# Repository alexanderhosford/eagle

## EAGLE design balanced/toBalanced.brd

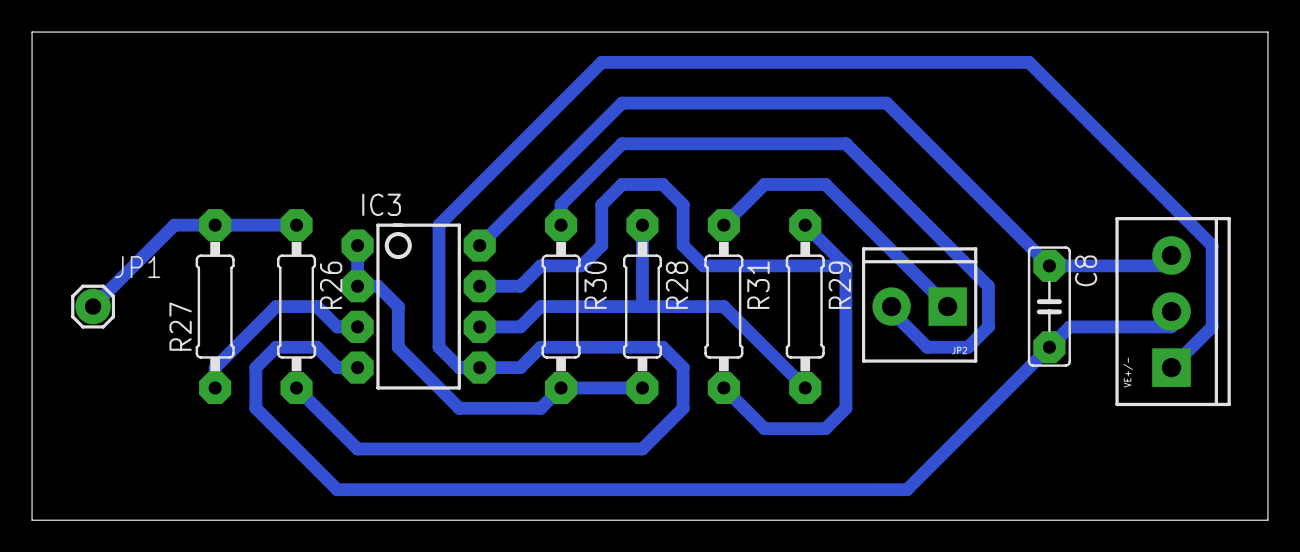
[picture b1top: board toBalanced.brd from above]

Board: 2 copper layers, 77.1 x 30.5 mm, 11 parts (0 on the bottom side), 10 nets.

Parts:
C8: 100nF; C050-025X075
IC3: TL072; DIP08
JP1: INPUT; 1X01
JP2: OUTPUT; SCREWTERMINAL-3.5MM-2
R26, R28, R29: 10k; 0207/10
R27: 2k2; 0207/10
R30, R31: 100r; 0207/10
VE+/-: POWER; SCREWTERMINAL-3.5MM-3

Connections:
15V+: C8.1, IC3.8, VE+/-.3
15V-: C8.2, IC3.4, VE+/-.2
GND: IC3.5, R26.2, VE+/-.1
unnamed: JP1.1, R26.1, R27.2
unnamed: IC3.7, R29.1, R31.2
unnamed: JP2.1, R31.1
unnamed: JP2.2, R30.1
unnamed: IC3.6, R28.1, R29.2
unnamed: IC3.1, IC3.2, R28.2, R30.2
unnamed: IC3.3, R27.1

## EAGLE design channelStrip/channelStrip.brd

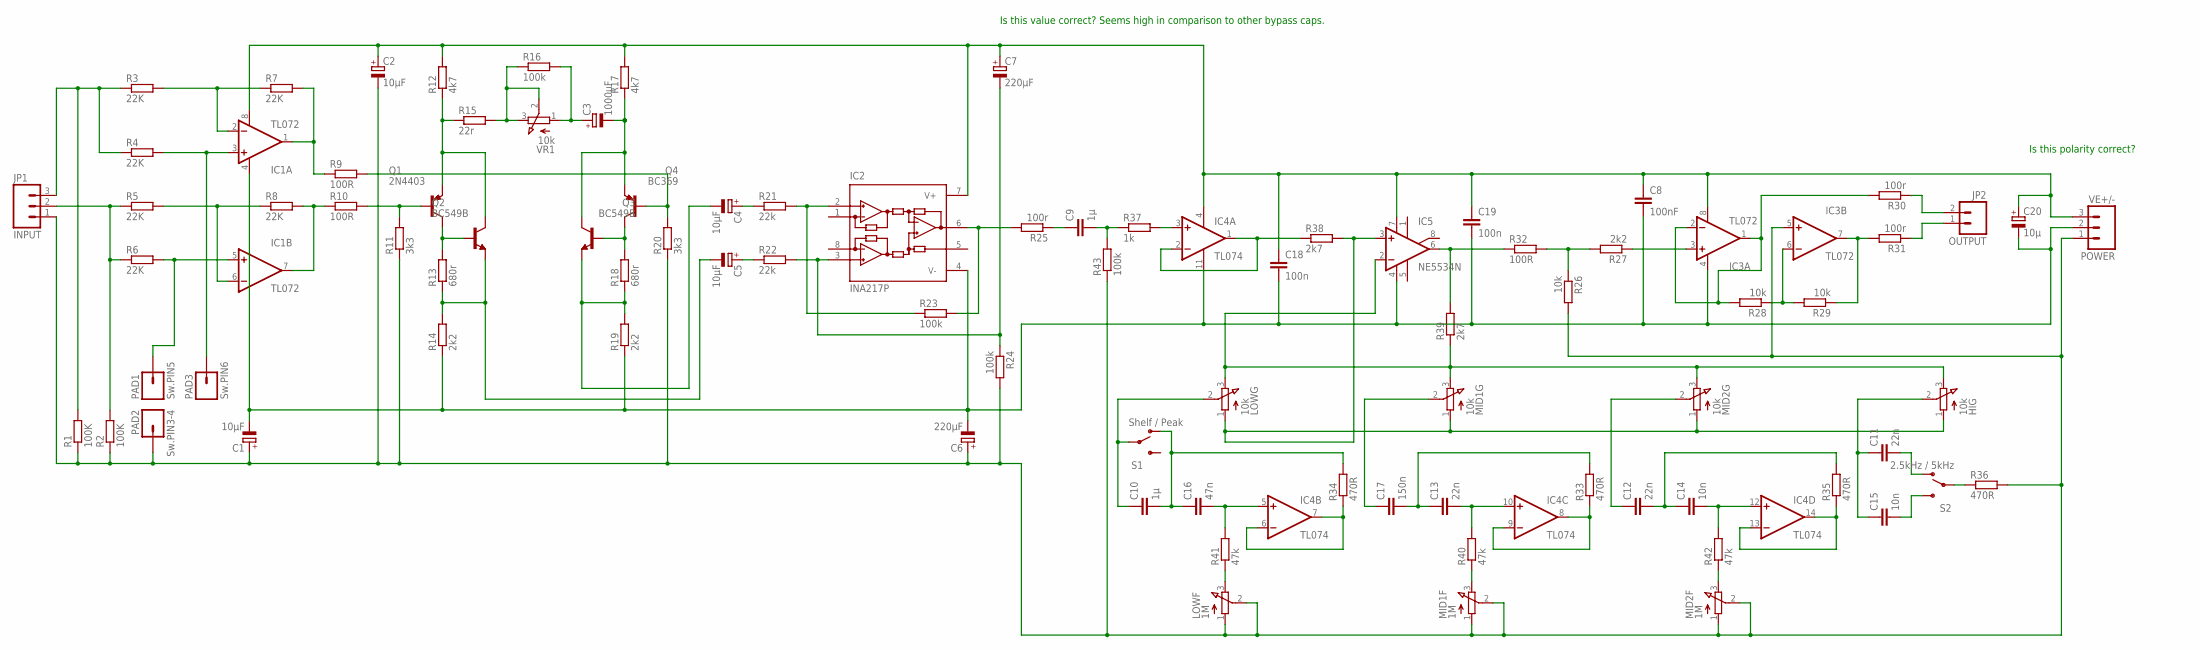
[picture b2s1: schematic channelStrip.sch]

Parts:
C1, C2: 10µF; E2,5-6
C3: 1000µF; E5-10,5
C4, C5: 10µF; E15-5
C6, C7: 220µF; E5-10,5
C8: 100nF; C050-025X075
C9, C10: 1µ; C050-025X075
C11, C12, C13: 22n; C050-025X075
C14, C15: 10n; C050-025X075
C16: 47n; C050-025X075
C17: 150n; C050-025X075
C18, C19: 100n; C050-025X075
C20: 10µ; E2,5-6E
HIG: 10k; 3RP/1610N
IC1, IC3: TL072; DIP08
IC2: INA217P; DIL08
IC4: TL074; DIL14
IC5: NE5534N; DIL08
JP1: INPUT; SCREWTERMINAL-3.5MM-3
JP2: OUTPUT; SCREWTERMINAL-3.5MM-2
LOWF: 1M; 3RP/1610N
LOWG: 10k; 3RP/1610N
MID1F, MID2F: 1M; 3RP/1610N
MID1G, MID2G: 10k; 3RP/1610N
PAD1: Sw.PIN5; 1X01_2MM
PAD2: Sw.PIN3-4; 1X01_2MM
PAD3: Sw.PIN6; 1X01_2MM
Q1: 2N4403; TO92-BCE
Q2, Q3: BC549B; TO92-EBC
Q4: BC369; TO92-BCE
R1, R2: 100K; 0207/10
R3, R4, R5, R6, R7, R8: 22K; 0207/10
R9, R10, R32: 100R; 0207/10
R11, R20: 3k3; 0207/10
R12, R17: 4k7; 0207/10
R13, R18: 680r; 0207/10
R14, R19, R27: 2k2; 0207/10
R15: 22r; 0207/10
R16, R23, R24, R43: 100k; 0207/10
R21, R22: 22k; 0207/10
R25, R30, R31: 100r; 0207/10
R26, R28, R29: 10k; 0207/10
R33, R34, R35, R36: 470R; 0207/10
R37: 1k; 0207/10
R38, R39: 2k7; 0207/10
R40, R41, R42: 47k; 0207/10
S1: Shelf / Peak; SWITCH-SPDT
S2: 2.5kHz / 5kHz; SWITCH-SPDT
VE+/-: POWER; SCREWTERMINAL-3.5MM-3
VR1: 10k; 3RP/1610N

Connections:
15V+: C2.+, C7.+, C8.1, C18.1, C19.1, C20.+, IC1.8 (V+), IC2.7 (V+), IC3.8 (V+), IC4.4 (V+), IC5.7 (V+), R12.2, R17.2, VE+/-.3
15V-: C1.-, C6.-, C8.2, C18.2, C19.2, C20.-, IC1.4 (V-), IC2.4 (V-), IC3.4 (V-), IC4.11 (V-), IC5.4 (V-), R14.1, R19.1, VE+/-.2
GND: C1.+, C2.-, C6.+, IC3.5 (+IN), JP1.1, LOWF.1 (A), LOWF.2 (S), MID1F.1 (A), MID1F.2 (S), MID2F.1 (A), MID2F.2 (S), PAD2.1, R1.1, R2.1, R11.1, R20.1, R24.2, R26.2, R36.2, R43.1, VE+/-.1
unnamed: C12.1, MID2G.2 (S)
unnamed: IC3.7 (OUT), R29.1, R31.2
unnamed: C10.2, C16.1, R34.2, S1.1 (O)
unnamed: C13.1, C17.2, R33.2
unnamed: C12.2, C14.1, R35.2
unnamed: C15.2, S2.3 (S)
unnamed: C11.2, S2.1 (O)
unnamed: R36.1, S2.2
unnamed: IC4.13 (-IN), IC4.14 (OUT), R35.1
unnamed: C14.2, IC4.12 (+IN), R42.2
unnamed: MID2F.3 (E), R42.1
unnamed: C9.1, R25.1
unnamed: C9.2, R37.1, R43.2
unnamed: IC4.3 (+IN), R37.2
unnamed: IC4.1 (OUT), IC4.2 (-IN), R38.1
unnamed: HIG.1 (A), IC5.3 (+IN), LOWG.1 (A), MID1G.1 (A), MID2G.1 (A), R38.2
unnamed: IC5.6 (OUT), R32.1, R39.2
unnamed: R26.1, R27.2, R32.2
unnamed: IC4.6 (-IN), IC4.7 (OUT), R34.1
unnamed: C16.2, IC4.5 (+IN), R41.2
unnamed: LOWF.3 (E), R41.1
unnamed: C10.1, LOWG.2 (S), S1.2
unnamed: IC4.8 (OUT), IC4.9 (-IN), R33.1
unnamed: C13.2, IC4.10 (+IN), R40.2
unnamed: MID1F.3 (E), R40.1
unnamed: HIG.3 (E), IC5.2 (-IN), LOWG.3 (E), MID1G.3 (E), MID2G.3 (E), R39.1
unnamed: C11.1, C15.1, HIG.2 (S)
unnamed: JP2.1, R31.1
unnamed: JP2.2, R30.1
unnamed: C7.-, IC2.3 (+IN), R22.2, R24.1
unnamed: IC3.6 (-IN), R28.1, R29.2
unnamed: IC3.1 (OUT), IC3.2 (-IN), R28.2, R30.2
unnamed: IC3.3 (+IN), R27.1
unnamed: C4.+, R21.1
unnamed: IC2.6 (OUT), R23.2, R25.2
unnamed: IC2.2 (-IN), R21.2, R23.1
unnamed: C5.+, R22.1
unnamed: R15.2, R16.1, VR1.2 (S), VR1.3 (E)
unnamed: C3.+, R16.2, VR1.1 (A)
unnamed: C3.-, Q3.C, Q4.E, R17.1
unnamed: Q1.E, Q2.C, R12.1, R15.1
unnamed: Q3.B, Q4.C, R18.2
unnamed: IC1.1 (OUT), R7.2, R9.1
unnamed: Q1.C, Q2.B, R13.2
unnamed: C5.-, Q2.E, R13.1, R14.2
unnamed: IC1.7 (OUT), R8.2, R10.1
unnamed: C4.-, Q3.E, R18.1, R19.2
unnamed: Q4.B, R9.2, R20.2
unnamed: Q1.B, R10.2, R11.2
unnamed: IC1.6 (-IN), R5.2, R8.1
unnamed: IC1.2 (-IN), R3.2, R7.1
unnamed: IC1.5 (+IN), PAD1.1, R6.2
unnamed: IC1.3 (+IN), PAD3.1, R4.2
unnamed: JP1.3, R1.2, R3.1, R4.1
unnamed: JP1.2, R2.2, R5.1, R6.1
VIA1: C17.1, MID1G.2 (S)

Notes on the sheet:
Is this polarity correct?
Is this value correct? Seems high in comparison to other bypass caps.

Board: 2 copper layers, 88 parts (0 on the bottom side), 59 nets, no tracks yet.

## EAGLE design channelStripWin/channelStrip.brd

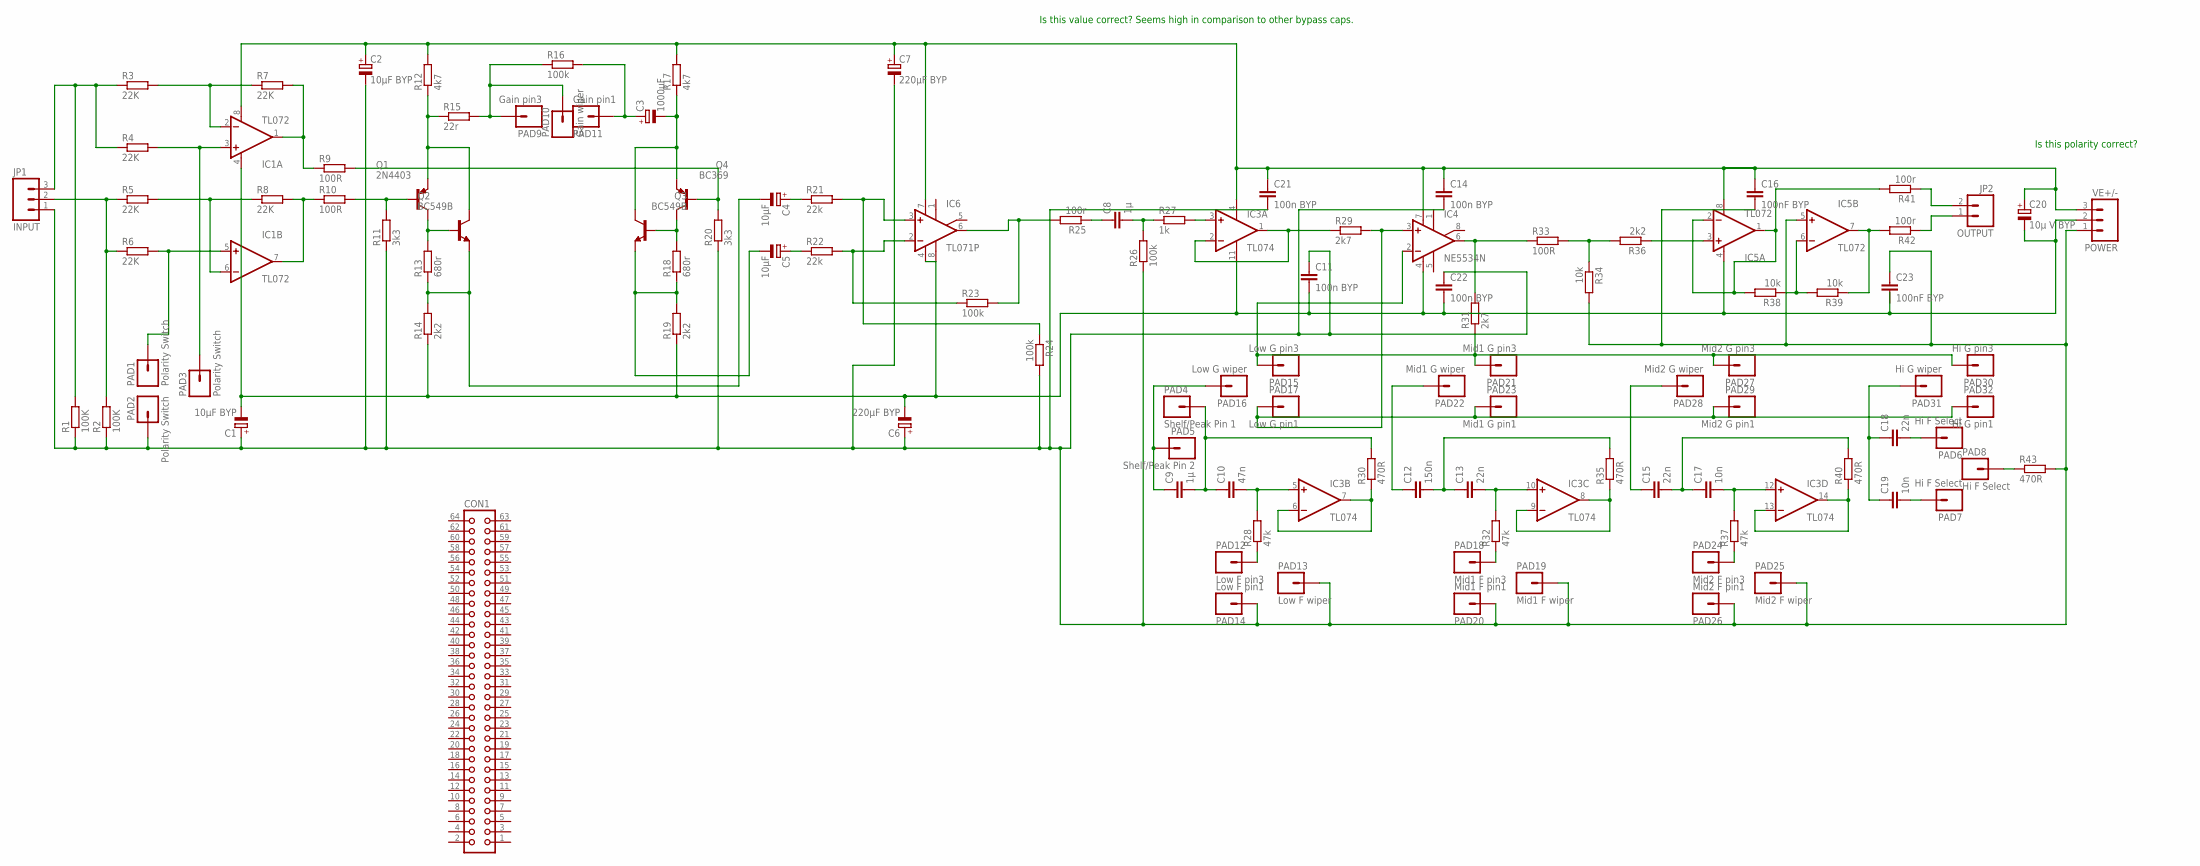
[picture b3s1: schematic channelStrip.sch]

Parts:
C1, C2: 10µF BYP; E2,5-6
C3: 1000µF; E5-10,5
C4, C5: 10µF; E15-5
C6, C7: 220µF BYP; E5-10,5
C8, C9: 1µ; C050-025X075
C10: 47n; C050-025X075
C11, C14, C21, C22: 100n BYP; C050-025X075
C12: 150n; C050-025X075
C13, C15, C18: 22n; C050-025X075
C16, C23: 100nF BYP; C050-025X075
C17, C19: 10n; C050-025X075
C20: 10µ V BYP; E2,5-6E
CON1: CON64
IC1, IC5: TL072; DIP08
IC3: TL074; DIL14
IC4: NE5534N; DIL08
IC6: TL071P; DIL08
JP1: INPUT; SCREWTERMINAL-3.5MM-3
JP2: OUTPUT; SCREWTERMINAL-3.5MM-2
PAD1, PAD2, PAD3: Polarity Switch; 1X01_2MM
PAD4: Shelf/Peak Pin 1; 1X01_2MM
PAD5: Shelf/Peak Pin 2; 1X01_2MM
PAD6, PAD7, PAD8: Hi F Select; 1X01_2MM
PAD9: Gain pin3; 1X01_2MM
PAD10: Gain wiper; 1X01_2MM
PAD11: Gain pin1; 1X01_2MM
PAD12: Low F pin3; 1X01_2MM
PAD13: Low F wiper; 1X01_2MM
PAD14: Low F pin1; 1X01_2MM
PAD15: Low G pin3; 1X01_2MM
PAD16: Low G wiper; 1X01_2MM
PAD17: Low G pin1; 1X01_2MM
PAD18: Mid1 F pin3; 1X01_2MM
PAD19: Mid1 F wiper; 1X01_2MM
PAD20: Mid1 F pin1; 1X01_2MM
PAD21: Mid1 G pin3; 1X01_2MM
PAD22: Mid1 G wiper; 1X01_2MM
PAD23: Mid1 G pin1; 1X01_2MM
PAD24: Mid2 F pin3; 1X01_2MM
PAD25: Mid2 F wiper; 1X01_2MM
PAD26: Mid2 F pin1; 1X01_2MM
PAD27: Mid2 G pin3; 1X01_2MM
PAD28: Mid2 G wiper; 1X01_2MM
PAD29: Mid2 G pin1; 1X01_2MM
PAD30: Hi G pin3; 1X01_2MM
PAD31: Hi G wiper; 1X01_2MM
PAD32: Hi G pin1; 1X01_2MM
Q1: 2N4403; TO92-BCE
Q2, Q3: BC549B; TO92-EBC
Q4: BC369; TO92-BCE
R1, R2: 100K; 0207/10
R3, R4, R5, R6, R7, R8: 22K; 0207/10
R9, R10, R33: 100R; 0207/10
R11, R20: 3k3; 0207/10
R12, R17: 4k7; 0207/10
R13, R18: 680r; 0207/10
R14, R19, R36: 2k2; 0207/10
R15: 22r; 0207/10
R16, R23, R24, R26: 100k; 0207/10
R21, R22: 22k; 0207/10
R25, R41, R42: 100r; 0207/10
R27: 1k; 0207/10
R28, R32, R37: 47k; 0207/10
R29, R31: 2k7; 0207/10
R30, R35, R40, R43: 470R; 0207/10
R34, R38, R39: 10k; 0207/10
VE+/-: POWER; SCREWTERMINAL-3.5MM-3

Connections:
15V+: C2.+, C7.+, C14.1, C16.1, C20.+, C21.1, IC1.8 (V+), IC3.4 (V+), IC4.7 (V+), IC5.8 (V+), IC6.7 (V+), R12.2, R17.2, VE+/-.3
15V-: C1.-, C6.-, C11.2, C20.-, C22.2, IC1.4 (V-), IC3.11 (V-), IC4.4 (V-), IC5.4 (V-), IC6.4 (V-), R14.1, R19.1, VE+/-.2
GND: C1.+, C2.-, C6.+, C7.-, C11.1, C14.2, C16.2, C21.2, C22.1, C23.1, IC5.5 (+IN), JP1.1, PAD2.1, PAD13.1, PAD14.1, PAD19.1, PAD20.1, PAD25.1, PAD26.1, R1.1, R2.1, R11.1, R20.1, R24.2, R26.1, R34.2, R43.2, VE+/-.1
unnamed: C15.1, PAD28.1
unnamed: IC5.7 (OUT), R39.1, R42.2
unnamed: C4.-, Q2.E, R13.1, R14.2
unnamed: C9.2, C10.1, PAD4.1, R30.2
unnamed: C12.2, C13.1, R35.2
unnamed: C15.2, C17.1, R40.2
unnamed: C19.2, PAD7.1
unnamed: C18.2, PAD6.1
unnamed: PAD8.1, R43.1
unnamed: IC3.13 (-IN), IC3.14 (OUT), R40.1
unnamed: C17.2, IC3.12 (+IN), R37.2
unnamed: PAD24.1, R37.1
unnamed: C8.1, R25.1
unnamed: C8.2, R26.2, R27.1
unnamed: IC3.3 (+IN), R27.2
unnamed: IC3.1 (OUT), IC3.2 (-IN), R29.1
unnamed: IC4.3 (+IN), PAD17.1, PAD23.1, PAD29.1, PAD32.1, R29.2
unnamed: IC4.6 (OUT), R31.2, R33.1
unnamed: R33.2, R34.1, R36.2
unnamed: IC3.6 (-IN), IC3.7 (OUT), R30.1
unnamed: C10.2, IC3.5 (+IN), R28.2
unnamed: PAD12.1, R28.1
unnamed: C9.1, PAD5.1, PAD16.1
unnamed: IC3.8 (OUT), IC3.9 (-IN), R35.1
unnamed: C13.2, IC3.10 (+IN), R32.2
unnamed: PAD18.1, R32.1
unnamed: IC4.2 (-IN), PAD15.1, PAD21.1, PAD27.1, PAD30.1, R31.1
unnamed: C18.1, C19.1, PAD31.1
unnamed: JP2.1, R42.1
unnamed: JP2.2, R41.1
unnamed: IC6.3 (+IN), R21.2, R24.1
unnamed: IC5.6 (-IN), R38.1, R39.2
unnamed: IC5.1 (OUT), IC5.2 (-IN), R38.2, R41.2
unnamed: IC5.3 (+IN), R36.1
unnamed: C4.+, R21.1
unnamed: IC6.6 (OUT), R23.2, R25.2
unnamed: IC6.2 (-IN), R22.2, R23.1
unnamed: C5.+, R22.1
unnamed: PAD9.1, PAD10.1, R15.2, R16.1
unnamed: C3.+, PAD11.1, R16.2
unnamed: C3.-, Q3.C, Q4.E, R17.1
unnamed: Q1.E, Q2.C, R12.1, R15.1
unnamed: Q3.B, Q4.C, R18.2
unnamed: IC1.1 (OUT), R7.2, R9.1
unnamed: Q1.C, Q2.B, R13.2
unnamed: IC1.7 (OUT), R8.2, R10.1
unnamed: C5.-, Q3.E, R18.1, R19.2
unnamed: Q4.B, R9.2, R20.2
unnamed: Q1.B, R10.2, R11.2
unnamed: IC1.6 (-IN), R5.2, R8.1
unnamed: IC1.2 (-IN), R3.2, R7.1
unnamed: IC1.5 (+IN), PAD1.1, R6.2
unnamed: IC1.3 (+IN), PAD3.1, R4.2
unnamed: JP1.3, R1.2, R3.1, R4.1
unnamed: JP1.2, R2.2, R5.1, R6.1
VIA1: C12.1, PAD22.1

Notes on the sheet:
Is this polarity correct?
Is this value correct? Seems high in comparison to other bypass caps.

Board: 2 copper layers, 110 parts (0 on the bottom side), 59 nets, no tracks yet.

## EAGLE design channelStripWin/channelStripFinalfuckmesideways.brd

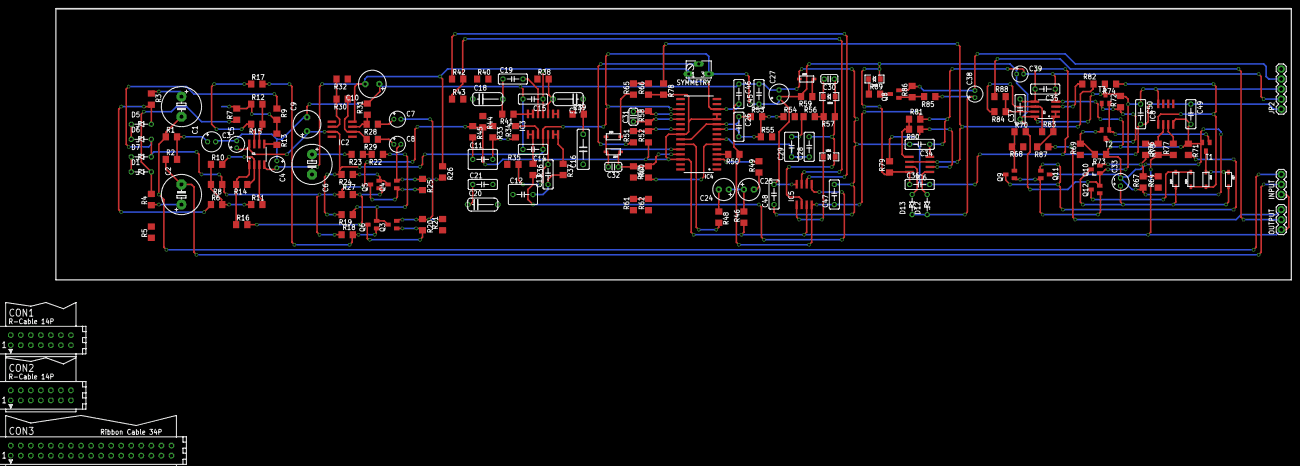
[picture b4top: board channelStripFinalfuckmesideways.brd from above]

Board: 2 copper layers, 312.4 x 68.6 mm, 174 parts (0 on the bottom side), 130 nets.

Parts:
C1, C2: 22µ 63V NP; E5-10,5
C3: 10µ 63V; E2-5
C4, C5: 10µF 25V; E1,8-4
C6: 1000µF 16V; E5-10,5
C7, C8: 10µF ≥25V; E1,8-4
C9, C10: 220µF ≥25V; E3,5-8
C11, C12: 1µ; C050-050X075
C13: 47n; C050-025X075
C14, C15, C26, C34, C35, C36, C37, C45, C46, C47, C48, C49, C50: 100n; C050-025X075
C16: 150n; C075-032X103
C17, C18, C20: 22n; C075-032X075
C19, C21: 10n; C050-025X075
C24, C25: 47µ 25V; E2,5-6
C27: 22µ 25V; E2-5
C28: 50n; C050-025X075
C29: 470n; C050-035X075
C30: 2n; C025-024X044
C31: 47p NPO 5%; C025-024X044
C32: 22p; C025-024X044
C33: 4µ7 35V; E2-4
C38: 10µ 25V; E1,8-4
C39: 10µ 35V; E1,8-4
CON1: EQ_CONTROLS; CON14
CON2: PRE_CONTROLS; CON14
CON3: COMP_CONTROLS; CON34
D1, D5, D6, D7: 10V; ZD-5-SMALLSILK
D12, D13: 12V; ZD-5-SMALLSILK
D14, D15, D16, D17, D18, D19, D20: 1N4148; SOD-123
IC1, IC7: TL072; SO08
IC2: TL071D; SO08
IC3: TL074; SO14
IC4: THAT4301P; SO30W
IC5: NE5532D; SO08
IC6: LM1458D; SO08
IC8: LM393D; SO08
INPUT: 1X03
JP2: POWER; 1X05
LED1, LED2: LED-1206
LED3: Peak; LED-1206
OUTPUT: 1X03
Q3, Q4, Q8: BC849; SOT23
Q5, Q6: MMBT4403; SOT23-BEC
Q9, Q11, Q12: MMBT3906; SOT23-BEC
Q10: LSK170A; SOT23
R1, R2: 6k8; R1206
R3, R4: 10R; R1206
R5, R56: 150R; R1206
R6, R7: 680R; R1206
R8, R9: 100K; R1206
R10, R11, R12, R13, R14, R15: 22K; R1206
R16, R17, R43: 100R; R1206
R18, R27: 3k3; R1206
R19, R24: 4k7; R1206
R20, R25: 680r; R1206
R21, R26, R82, R86, R89: 2k2; R1206
R22: 22r; R1206
R23, R30, R31, R33, R45: 100k; R1206
R28, R29, R79, R81, R85: 22k; R1206
R32, R87, R88: 100r; R1206
R34: 1k; R1206
R35, R38, R40: 47k; R1206
R36, R42: 2k7; R1206
R37, R39, R41, R44: 470R; R1206
R46, R49: 28k8; R1206
R48, R58: 20k; R1206
R50, R57: 2M; R1206
R51: 300k 5%; R1206
R52: 51R 5%; R1206
R53, R60: 5k1 3300ppm; R1206
R54, R62, R63, R64: 30k1; R1206
R55, R61: 590k; R1206
R59: 220k; R1206
R65: 1k4; R1206
R66: 15k; R1206
R67, R74: 5k1; R1206
R68: 127k; R1206
R69: 12k7; R1206
R70: 510R; R1206
R71: 18M; R1206
R72: 1M8; R1206
R73: 51R; R1206
R75, R76, R78, R80, R83, R84: 10k; R1206
R77: 30k; R1206
SYMMETRY: 50k; B64W
T1, T2: MMBT3904; SOT23-BEC
T3: MBT3904; SOT23-BEC

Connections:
48V2: CON2.2, JP2.5
+12V: C5.+, C9.+, C14.1, C27.+, C36.1, C37.1, C39.+, C45.1, C48.2, C50.1, IC1.8, IC2.7, IC3.4, IC4.18, IC5.8, IC6.8, IC7.8, IC8.8, JP2.3, LED3.A, R19.2, R24.2, R59.2, R79.1, SYMMETRY.E
-12V: C4.-, C10.-, C15.1, C34.1, C35.1, C39.-, C46.2, C47.1, C49.2, IC1.4, IC2.4, IC3.11, IC4.13, IC5.4, IC6.4, IC7.4, IC8.4, JP2.2, R21.1, R26.1, R50.1, R81.2, SYMMETRY.A
C_ATTACK1: CON3.8, R72.2, T3.C
C_ATTACK2: CON3.10, R69.1
C_ATTACK3: C33.-, CON3.12, R67.1, R73.1, T1.E
C_GAIN2: CON3.21, R55.2
C_RATIO2: CON3.4, R65.2, R66.2
C_RELEASE1: CON3.14, Q10.1, Q12.E, R70.2, R74.2
C_RELEASE2: CON3.16, R68.1
C_RELEASE3: CON3.18, Q11.C, R71.1
C_THRESH2: CON3.27, R61.1
EQ1: CON1.1, IC5.5, R36.2
EQ2: CON1.2, IC5.6, R42.1
EQ3: C12.1, CON1.3
EQ4: C12.2, C13.1, CON1.4, R37.2
EQ5: CON1.5, R35.1
EQ7: C16.1, CON1.7
EQ8: CON1.8, R38.1
EQ9: C18.1, CON1.9
EQ10: CON1.10, R40.1
EQ11: C20.1, C21.1, CON1.11
EQ12: C20.2, CON1.12
EQ13: C21.2, CON1.13
EQ14: CON1.14, R44.1
EQ_VCA1: CON3.1, R32.1
EQ_VCA2: C11.1, CON3.3, R45.2
EQ_VCA3: C31.2, CON3.5, IC4.19, R58.2
EQ_VCA4: CON3.7, R43.2
EQ_VCA5: C24.+, C25.+, CON3.9, R46.2
EQ_VCA8: CON3.15, IC6.3, IC6.6, R78.1, R82.2
GNDIO: D6.A, D7.A, IC4.11, IC4.12, IC4.23, IC4.28, IC5.3, INPUT.1, OUTPUT.1, R8.1, R9.1, R18.1, R27.1, R33.1, R44.2, R45.1, R46.1, R52.1, R66.1, R76.1, R77.1, R78.2
KNEE1: CON3.24, D20.A, R59.1
KNEE2: CON3.26, R62.1
KNEE3: CON3.32, R63.2
KNEE4: CON3.34, D15.A, R65.1
unnamed: IC7.7, R84.1, R88.2
unnamed: C7.-, Q3.2, R20.1, R21.2
unnamed: C16.2, C17.1, R39.2
unnamed: C18.2, C19.1, R41.2
unnamed: IC3.13, IC3.14, R41.1
unnamed: C19.2, IC3.12, R40.2
unnamed: C11.2, R33.2, R34.1
unnamed: IC3.3, R34.2
unnamed: IC3.1, IC3.2, R36.1
unnamed: IC5.7, R42.2, R43.1
unnamed: Q8.1, R85.2, R86.1
unnamed: C1.+, R3.1
unnamed: IC3.6, IC3.7, R37.1
unnamed: C13.2, IC3.5, R35.2
unnamed: IC3.8, IC3.9, R39.1
unnamed: C2.+, R4.1
unnamed: C17.2, IC3.10, R38.2
unnamed: IC6.2, R79.2, R80.1
unnamed: C1.-, INPUT.3, R1.1
unnamed: C2.-, INPUT.2, R2.1
unnamed: OUTPUT.2, R88.1
unnamed: OUTPUT.3, R87.1
unnamed: IC2.3, R28.2, R31.1
unnamed: IC7.6, R83.1, R84.2
unnamed: IC7.1, IC7.2, R83.2, R87.2
unnamed: IC7.3, R82.1
unnamed: C7.+, R28.1
unnamed: IC2.6, R30.2, R32.2
unnamed: IC2.2, R29.2, R30.1
unnamed: C8.+, R29.1
unnamed: C6.-, Q4.3, Q5.E, R24.1
unnamed: Q3.3, Q6.E, R19.1, R22.1
unnamed: Q4.1, Q5.C, R25.2
unnamed: IC1.1, R14.2, R16.1
unnamed: Q3.1, Q6.C, R20.2
unnamed: IC6.5, R80.2, R81.1
unnamed: IC1.7, R15.2, R17.1
unnamed: C8.-, Q4.2, R25.1, R26.2
unnamed: Q5.B, R16.2, R27.2
unnamed: Q6.B, R17.2, R18.2
unnamed: IC1.6, R12.2, R15.1
unnamed: D5.C, D6.C
unnamed: IC1.2, R10.2, R14.1
unnamed: D1.C, D7.C
unnamed: Q8.3, R89.2
unnamed: C38.+, D12.C, D13.C, R85.1
unnamed: LED3.C, R89.1
unnamed: D12.A, IC6.1
unnamed: D13.A, IC6.7
unnamed: IC4.25, R48.2
unnamed: C24.-, R48.1
unnamed: R51.1, SYMMETRY.S
unnamed: IC4.22, R51.2, R52.2
unnamed: C31.1, IC4.20, R58.1
unnamed: C26.1, IC4.10, IC4.24, R53.1
unnamed: C26.2, IC4.9, R53.2, R54.1, R55.1
unnamed: C29.2, R56.1
unnamed: C28.1, C29.1, IC4.7
unnamed: C28.2, C30.1, IC5.2, LED1.C, LED2.A, R57.1
unnamed: C30.2, IC5.1, LED1.A, LED2.C, R56.2, R57.2
unnamed: IC4.4, R50.2
unnamed: IC4.3, R49.2
unnamed: C25.-, R49.1
unnamed: IC4.6, R60.1
unnamed: C32.1, D14.C, IC4.27, R60.2, R61.2, R62.2, R63.1
unnamed: C32.2, D14.A, D15.C, IC4.26
unnamed: Q10.2, R64.2, R67.2, R75.2
unnamed: C33.+, D17.A, D18.C, Q10.3
unnamed: D16.C, D17.C, T1.C
unnamed: D18.A, D19.A, Q12.C
unnamed: D16.A, D19.C, IC8.1, R74.1
unnamed: T1.B, T2.B, T3.E
unnamed: R69.2, R73.2, T2.E
unnamed: R72.1, T2.C, T3.B
unnamed: Q9.B, Q11.E, Q12.B
unnamed: Q9.C, Q11.B, R71.2
unnamed: Q9.E, R68.2, R70.1
unnamed: IC8.2, R75.1, R76.2
PAD1: CON2.4, R5.1
PAD2: CON2.6, R6.2, R8.2, R10.1, R11.1
PAD3: CON2.8, D5.A, R3.2, R6.1
PAD4: CON2.10, R5.2
PAD5: CON2.12, R7.2, R9.2, R12.1, R13.1
PAD6: CON2.14, D1.A, R4.2, R7.1
PE: C3.-, C4.+, C5.-, C9.-, C10.+, C14.2, C15.2, C27.-, C34.2, C35.2, C36.2, C37.2, C45.2, C46.1, C47.2, C48.1, C49.1, C50.2, D20.C, IC7.5, JP2.1, R31.2
PEAKGND: C38.-, JP2.4, Q8.2, R86.2
POLARITY1: CON2.3, IC1.5, R13.2
POLARITY2: CON2.5, IC1.3, R11.2
PRE1: C3.+, R1.2, R2.2
P_GAIN1: CON2.9, R22.2, R23.1
P_GAIN3: C6.+, CON2.13, R23.2
VARMAN1: CON3.20, R54.2
VARMAN2: CON3.22, R64.1
VARMAN3: CON3.28, IC8.3, R77.2

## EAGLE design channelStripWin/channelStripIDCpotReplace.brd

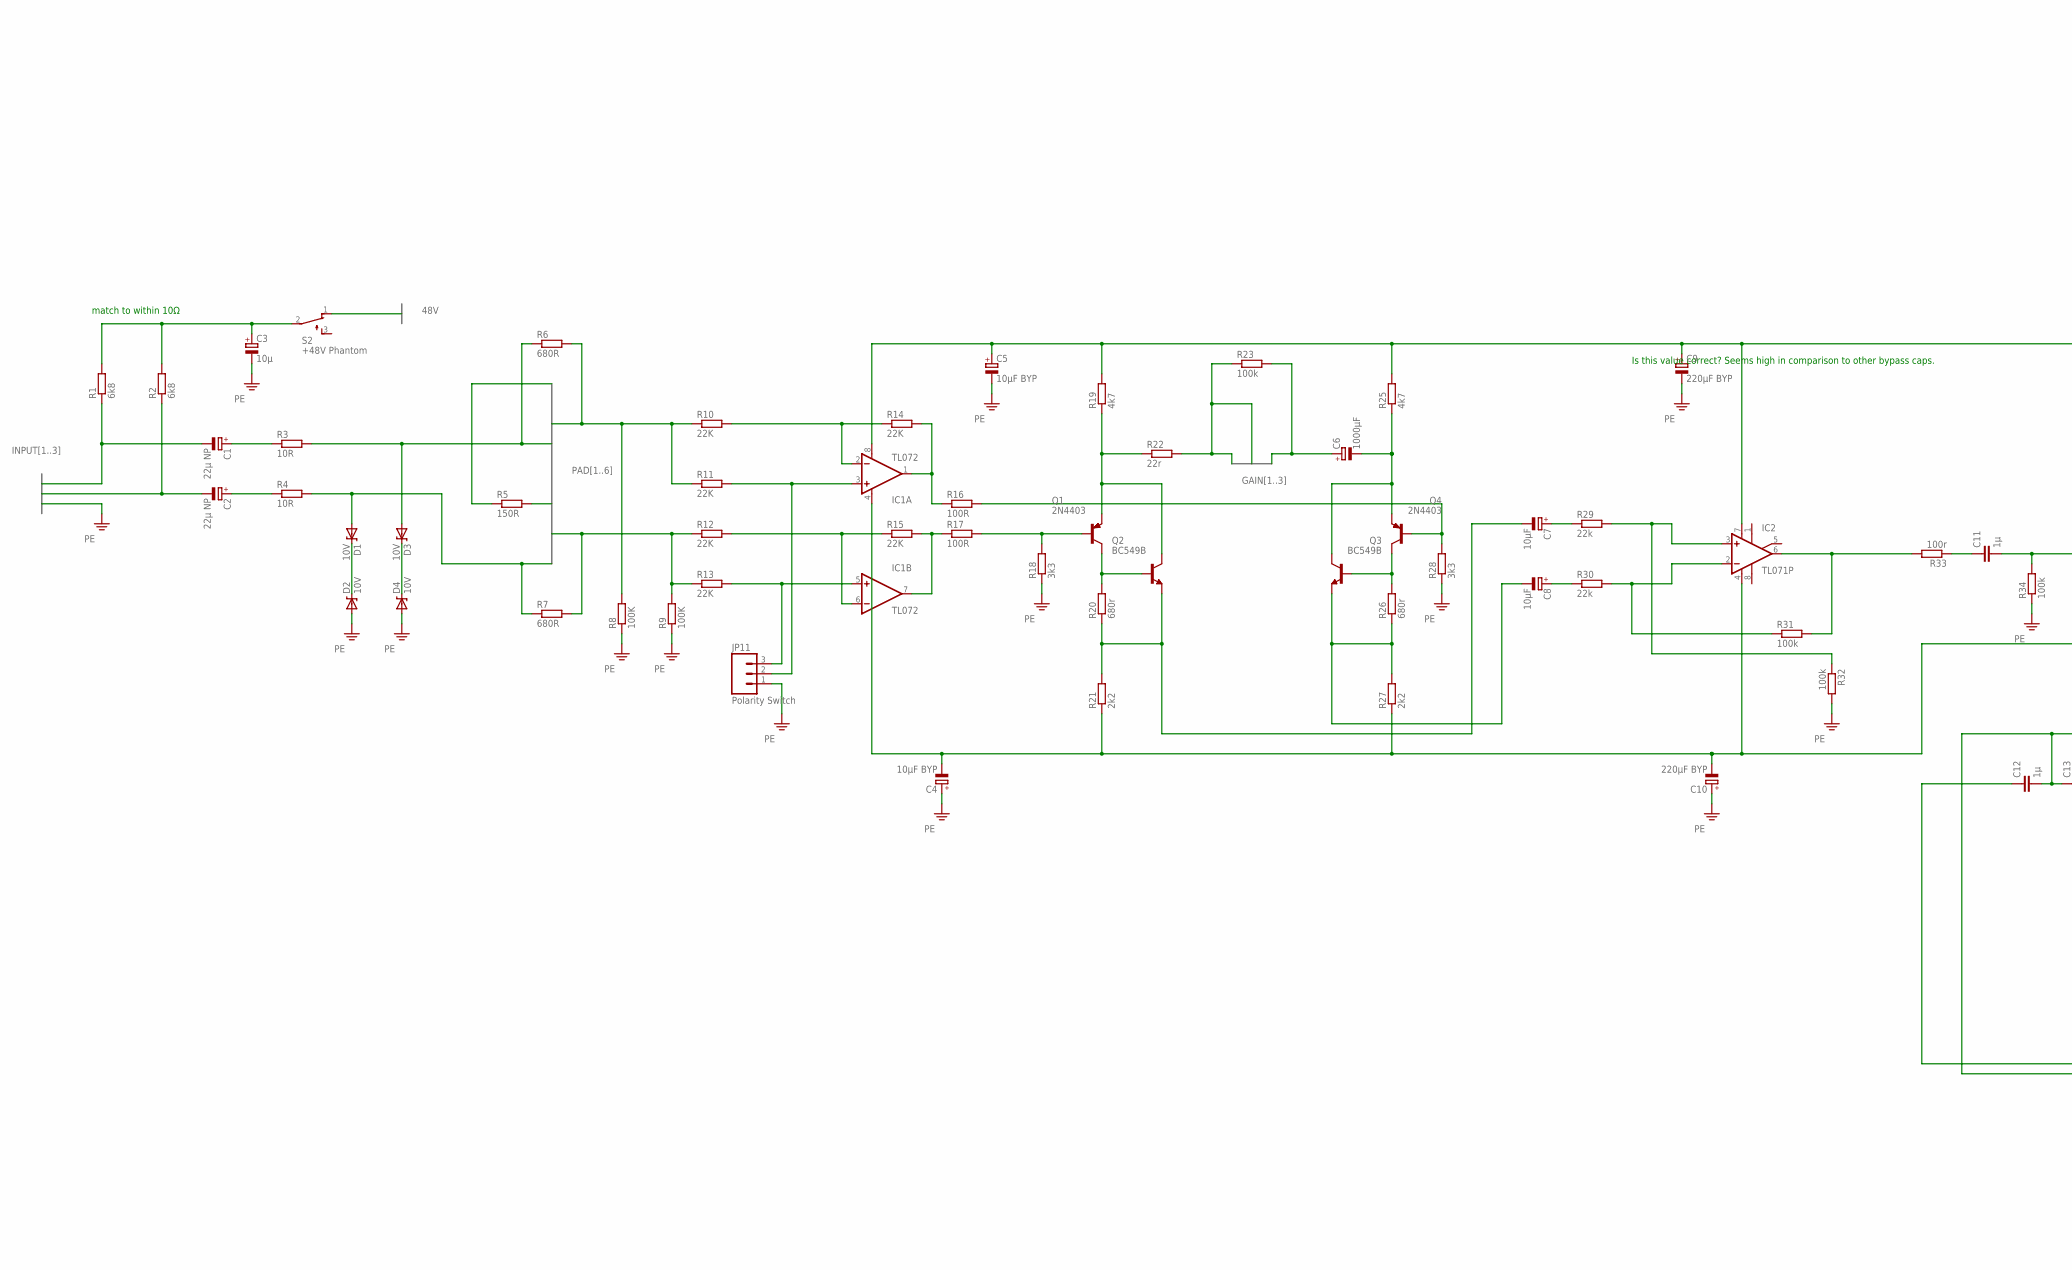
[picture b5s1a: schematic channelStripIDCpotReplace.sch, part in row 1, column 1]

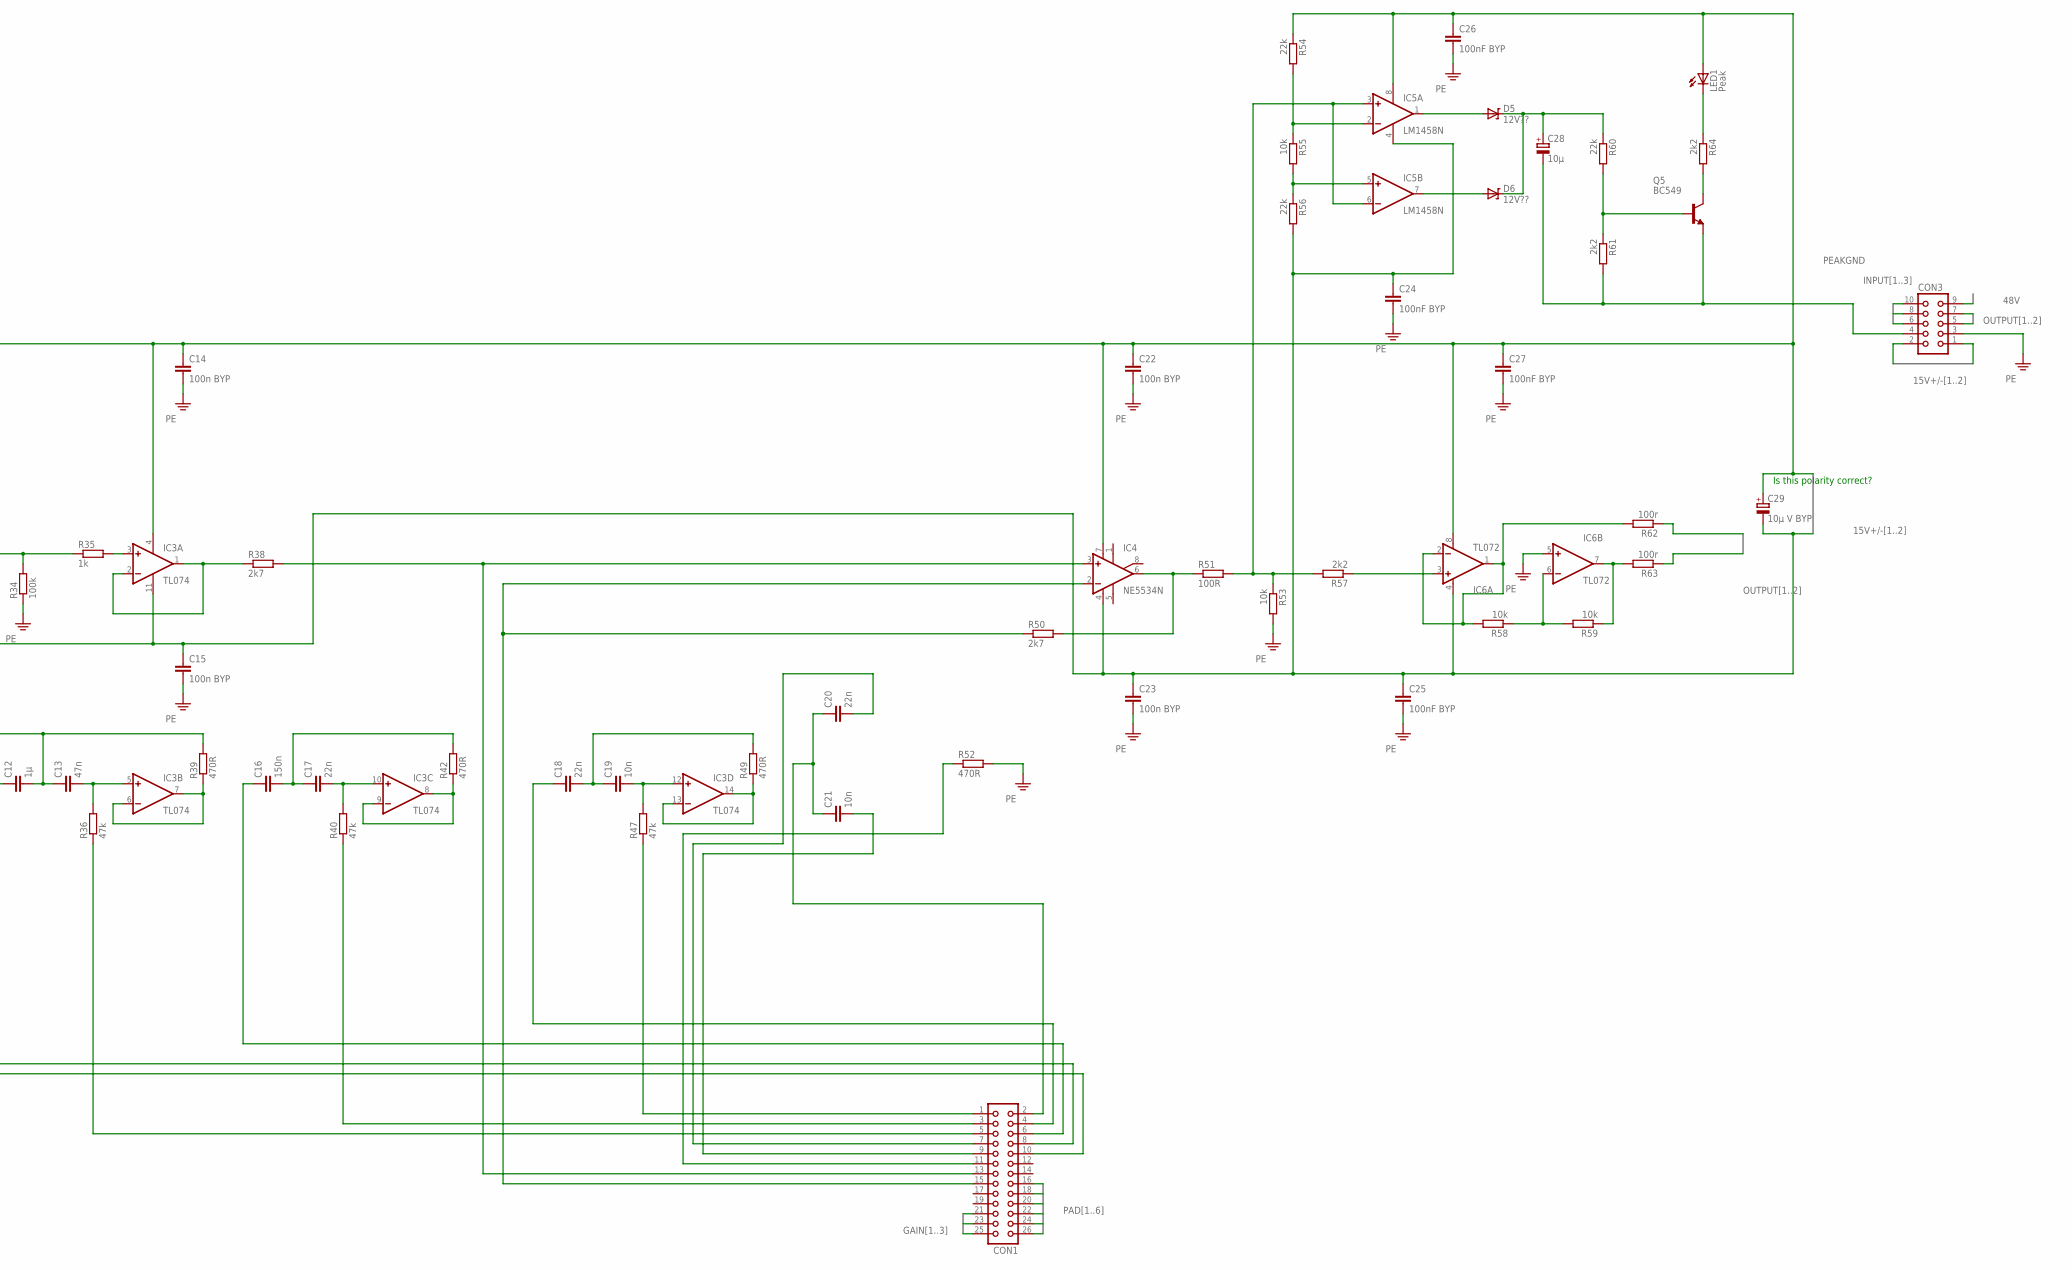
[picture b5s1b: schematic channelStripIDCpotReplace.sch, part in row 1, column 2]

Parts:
C1, C2: 22µ NP; E2,5-5
C3: 10µ; E2,5-6
C4, C5: 10µF BYP; E2,5-6
C6: 1000µF; E5-10,5
C7, C8: 10µF; E15-5
C9, C10: 220µF BYP; E5-10,5
C11, C12: 1µ; C050-025X075
C13: 47n; C050-025X075
C14, C15, C22, C23: 100n BYP; C050-025X075
C16: 150n; C050-025X075
C17, C18, C20: 22n; C050-025X075
C19, C21: 10n; C050-025X075
C24, C25, C26, C27: 100nF BYP; C050-025X075
C28: 10µ; E2,5-6E
C29: 10µ V BYP; E2,5-6E
CON1: CON26
CON3: CON10
D1, D2, D3, D4: 10V; DIODE-ZENER
D5, D6: 12V??; DIODE-ZENER
IC1, IC6: TL072; DIP08
IC2: TL071P; DIL08
IC3: TL074; DIL14
IC4: NE5534N; DIL08
IC5: LM1458N; DIL08
JP11: Polarity Switch; 1X03
LED1: Peak; LED3MM-NS
Q1, Q4: 2N4403; TO92-BCE
Q2, Q3: BC549B; TO92-EBC
Q5: BC549; TO92-EBC
R1, R2: 6k8; 0207/10
R3, R4: 10R; 0207/10
R5: 150R; 0207/10
R6, R7: 680R; 0207/10
R8, R9: 100K; 0207/10
R10, R11, R12, R13, R14, R15: 22K; 0207/10
R16, R17, R51: 100R; 0207/10
R18, R28: 3k3; 0207/10
R19, R25: 4k7; 0207/10
R20, R26: 680r; 0207/10
R21, R27, R57, R61, R64: 2k2; 0207/10
R22: 22r; 0207/10
R23, R31, R32, R34: 100k; 0207/10
R29, R30, R54, R56, R60: 22k; 0207/10
R33, R62, R63: 100r; 0207/10
R35: 1k; 0207/10
R36, R40, R47: 47k; 0207/10
R38, R50: 2k7; 0207/10
R39, R42, R49, R52: 470R; 0207/10
R53, R55, R58, R59: 10k; 0207/10
S2: +48V Phantom; TL3XPO

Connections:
15V+/-1: C4.-, C10.-, C15.1, C23.1, C24.1, C25.1, C29.-, CON3.1, IC1.4 (V-), IC2.4 (V-), IC3.11 (V-), IC4.4 (V-), IC5.4 (V-), IC6.4 (V-), R21.1, R27.1, R56.2
15V+/-2: C5.+, C9.+, C14.1, C22.1, C26.1, C27.1, C29.+, CON3.2, IC1.8 (V+), IC2.7 (V+), IC3.4 (V+), IC4.7 (V+), IC5.8 (V+), IC6.8 (V+), LED1.A, R19.2, R25.2, R54.1
48V: CON3.9, S2.1 (O)
GAIN1: C6.+, CON1.21, R23.2
GAIN2: CON1.23, CON1.25, R22.2, R23.1
GND: C3.-, C4.+, C5.-, C9.-, C10.+, C14.2, C15.2, C22.2, C23.2, C24.2, C25.2, C26.2, C27.2, D2.P$2 (A), D4.P$2 (A), IC6.5 (+IN), JP11.1, R8.1, R9.1, R18.1, R28.1, R32.2, R34.1, R52.2, R53.2
INPUT1: C1.-, CON3.10, R1.1
INPUT2: C2.-, CON3.8, R2.1
INPUT3: CON3.6
unnamed: C18.1, CON1.4
unnamed: IC6.7 (OUT), R59.1, R63.2
unnamed: C7.-, Q2.E, R20.1, R21.2
unnamed: C16.2, C17.1, R42.2
unnamed: C18.2, C19.1, R49.2
unnamed: C21.2, CON1.9
unnamed: C20.2, CON1.7
unnamed: CON1.11, R52.1
unnamed: IC3.13 (-IN), IC3.14 (OUT), R49.1
unnamed: C19.2, IC3.12 (+IN), R47.2
unnamed: CON1.3, R40.1
unnamed: C11.1, R33.1
unnamed: C11.2, R34.2, R35.1
unnamed: IC3.3 (+IN), R35.2
unnamed: IC3.1 (OUT), IC3.2 (-IN), R38.1
unnamed: CON1.15, IC4.2 (-IN), R50.1
unnamed: IC4.6 (OUT), R50.2, R51.1
unnamed: Q5.B, R60.2, R61.1
unnamed: C1.+, R3.1
unnamed: IC3.6 (-IN), IC3.7 (OUT), R39.1
unnamed: C13.2, IC3.5 (+IN), R36.2
unnamed: CON1.5, R36.1
unnamed: C12.1, CON1.8
unnamed: IC3.8 (OUT), IC3.9 (-IN), R42.1
unnamed: C2.+, R4.1
unnamed: C17.2, IC3.10 (+IN), R40.2
unnamed: CON1.1, R47.1
unnamed: IC5.2 (-IN), R54.2, R55.1
unnamed: C3.+, R1.2, R2.2, S2.2
unnamed: IC2.3 (+IN), R29.2, R32.1
unnamed: IC6.6 (-IN), R58.1, R59.2
unnamed: IC6.1 (OUT), IC6.2 (-IN), R58.2, R62.2
unnamed: IC6.3 (+IN), R57.1
unnamed: C20.1, C21.1, CON1.2
unnamed: C7.+, R29.1
unnamed: IC2.6 (OUT), R31.2, R33.2
unnamed: IC2.2 (-IN), R30.2, R31.1
unnamed: C8.+, R30.1
unnamed: C6.-, Q3.C, Q4.E, R25.1
unnamed: Q1.E, Q2.C, R19.1, R22.1
unnamed: Q3.B, Q4.C, R26.2
unnamed: IC1.1 (OUT), R14.2, R16.1
unnamed: Q1.C, Q2.B, R20.2
unnamed: IC5.5 (+IN), R55.2, R56.1
unnamed: IC1.7 (OUT), R15.2, R17.1
unnamed: C8.-, Q3.E, R26.1, R27.2
unnamed: Q4.B, R16.2, R28.2
unnamed: Q1.B, R17.2, R18.2
unnamed: IC1.6 (-IN), R12.2, R15.1
unnamed: D3.P$1 (C), D4.P$1 (C)
unnamed: IC1.2 (-IN), R10.2, R14.1
unnamed: IC1.5 (+IN), JP11.3, R13.2
unnamed: IC1.3 (+IN), JP11.2, R11.2
unnamed: D1.P$1 (C), D2.P$1 (C)
unnamed: Q5.C, R64.2
unnamed: C28.+, D5.P$1 (C), D6.P$1 (C), R60.1
unnamed: LED1.K (C), R64.1
unnamed: D5.P$2 (A), IC5.1 (OUT)
unnamed: D6.P$2 (A), IC5.7 (OUT)
unnamed: IC5.3 (+IN), IC5.6 (-IN), R51.2, R53.1, R57.2
unnamed: CON1.13, IC4.3 (+IN), R38.2
unnamed: C16.1, CON1.6
unnamed: C12.2, C13.1, CON1.10, R39.2
OUTPUT1: CON3.5, R63.1
OUTPUT2: CON3.7, R62.1
PAD1: CON1.16, R5.1
PAD2: CON1.18, R6.2, R8.2, R10.1, R11.1
PAD3: CON1.20, D3.P$2 (A), R3.2, R6.1
PAD4: CON1.22, R5.2
PAD5: CON1.24, R7.2, R9.2, R12.1, R13.1
PAD6: CON1.26, D1.P$2 (A), R4.2, R7.1
PE: CON3.3
PEAKGND: C28.-, CON3.4, Q5.E, R61.2

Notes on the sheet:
Is this polarity correct?
Is this value correct? Seems high in comparison to other bypass caps.
match to within 10Ω

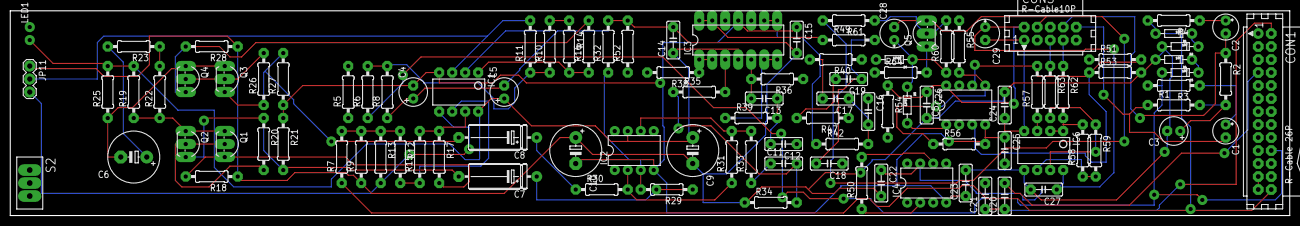
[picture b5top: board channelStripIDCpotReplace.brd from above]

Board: 2 copper layers, 250.0 x 40.0 mm, 107 parts (0 on the bottom side), 80 nets.

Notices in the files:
parts and their libraries:
SparkFun: Licensing: CC v3.0 Share-Alike You are welcome to use this library for commercial purposes.
